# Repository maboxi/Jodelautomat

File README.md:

# Jodelautomat

Der Jodelautomat ist eine Musikbox, welche ohne professionelles Vorwissen entworfen und gebaut wurde.
Das Ziel dieses Repositories ist es, einzelne Aspekte des Jodelautomats neu zu entwerfen, um letztendlich eine verbesserte Version bauen zu können.

## Was kann der Jodelautomat alles?

Derzeit hat der Jodelautomat zwei Funktionen:
 - Musik wiedergeben: der Jodelautomat besitzt einen 3.5mm Klinkeneingang, welcher einen Verstärker (2x50W Main Drivers+ 100W Subwoofer) nutzt, um über zwei in das Gehäuse eingebaute Lautsprecher und einen in den Gehäuseboden integrierten Subwoofer Musik abzuspielen
 - LED-Beleuchtung: der Jodelautomat besitzt 3 LED-Bereiche (unten am Gehäuse, an den zwei Hauptlautsprechern an der Vorderseite und an der Bedienfläche des Jodelautomats), deren Farben entweder manuell ausgewählt oder von einem Mikrocontroller (für "Sound-To-Light") angesteuert werden können; das alte Sound-To-Light-System funtioniert jedoch nur grenzwertig

## Was soll der Jodelautomat alles können?

Ideen für Funktionen (+ Status):
 - Musik-Wiedergabe über Bluetooth
 - (WIP) Funktionierendes Sound-To-Light + LED-Ansteuerung: **JAVS** = Jodelautomat Visual System
 - besseres Gehäuse (leichter, an gewählte Lautsprecher angepasst)
 - neuen Akku + Ladefunktion + Netzadapter

## Repo TODO:
 - Bilder

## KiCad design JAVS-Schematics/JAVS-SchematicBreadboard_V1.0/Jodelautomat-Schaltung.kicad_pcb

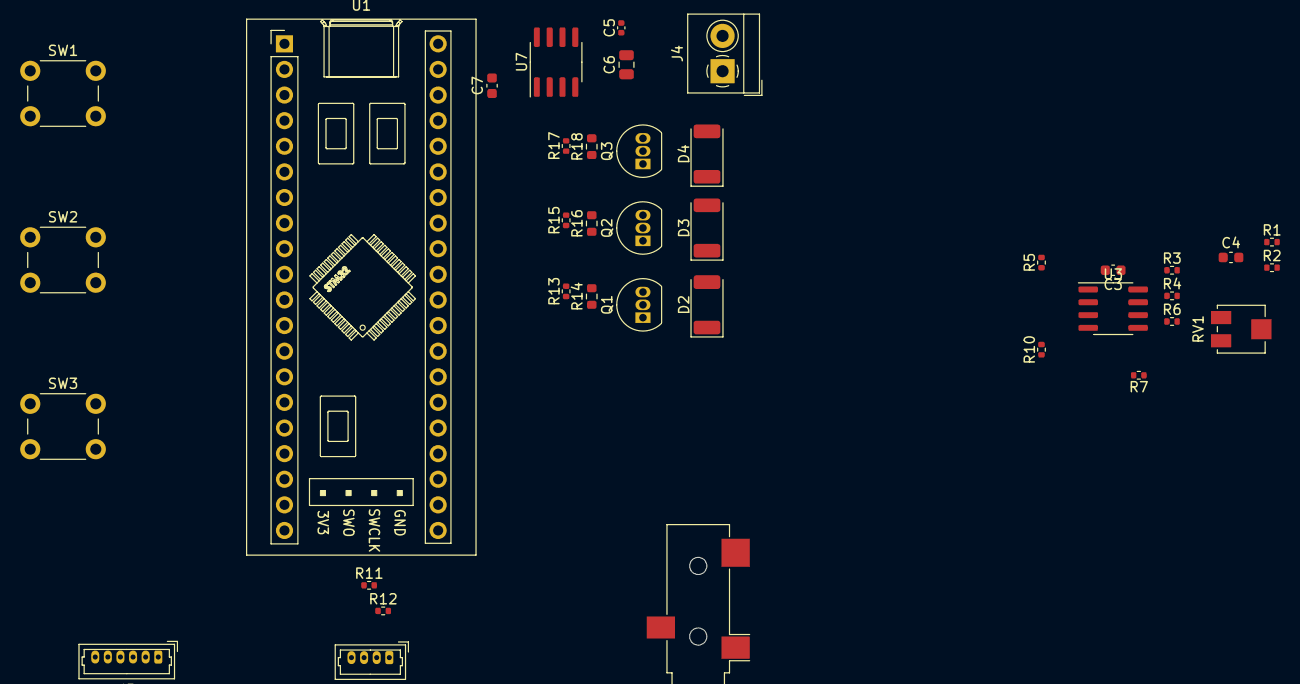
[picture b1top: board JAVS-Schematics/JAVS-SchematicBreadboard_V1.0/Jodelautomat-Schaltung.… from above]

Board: 2 copper layers, 38 parts (0 on the bottom side), 33 nets, no tracks yet.

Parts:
C3: 100n; C_0603_1608Metric
C4, C7: 10u; C_0603_1608Metric
C5: 10uF; C_0402_1005Metric
C6: 10uF; C_0805_2012Metric
D2: LED_R; LED_2010_5025Metric
D3: LED_G; LED_2010_5025Metric
D4: LED_B; LED_2010_5025Metric
J1: AudioJack3; Jack_3.5mm_CUI_SJ-3523-SMT_Horizontal
J2: I2C_5V_01x04; Molex_PicoBlade_53047-0410_1x04_P1.25mm_Vertical
J4: Screw_Terminal_01x02; TerminalBlock_4Ucon_1x02_P3.50mm_Horizontal
J5: USART_Full_01x06; Molex_PicoBlade_53047-0610_1x06_P1.25mm_Vertical
Q1, Q2, Q3: BC337; TO-92_Inline
R1, R2: 50k; R_0402_1005Metric
R3, R4, R5, R6, R7, R10: 100k; R_0402_1005Metric
R11, R12, R13, R15, R17: 10k; R_0402_1005Metric
R14: 120R; R_0603_1608Metric
R16, R18: 30R; R_0603_1608Metric
RV1: 100k; Potentiometer_Bourns_3314J_Vertical
SW1: BTN_A; SW_PUSH_6mm
SW2: BTN_B; SW_PUSH_6mm
SW3: BTN_C; SW_PUSH_6mm
U1: BlackPill_F401CCU6_SORTED; BlackPill_F401CCU6
U3: LM358; SOIC-8_3.9x4.9mm_P1.27mm
U7: ICL7660; SOIC-8_3.9x4.9mm_P1.27mm

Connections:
+3.3V: C7.1, D2.2 (A), D3.2 (A), D4.2 (A), J5.4, R10.1, U1.20 (3.3V), U1.21 (VBAT), U1.38 (3.3V)
+5V: C3.2, C4.2, J2.3, J4.1, R11.1, R12.1, U1.18 (5V), U1.40 (5V), U3.4 (V-), U7.8 (V+)
-5V: C3.1, C4.1, C6.2, U3.8 (V+), U7.5 (VOUT)
ADC_IN: R6.2, U1.28 (A2), U3.1
BTN_A: SW1.1, U1.1 (B12)
BTN_B: SW2.1, U1.2 (B13)
BTN_C: SW3.1, U1.3 (B14)
GND: C6.1, C7.2, J1.T, J2.4, J4.2, J5.6, R5.2, R14.1, R16.1, R18.1, SW1.2, SW2.2, SW3.2, U1.19 (G), U1.39 (G), U3.3 (+), U3.5 (+), U7.3 (GND)
LED_1_B: R17.1, U1.35 (B1)
LED_1_G: R15.1, U1.34 (B0)
LED_1_R: R13.1, U1.29 (A3)
unnamed: D2.1 (K), Q1.1 (C)
unnamed: D3.1 (K), Q2.1 (C)
unnamed: D4.1 (K), Q3.1 (C)
unnamed: J1.R, R2.1
unnamed: J1.S, R1.1
unnamed: J2.1, R12.2
unnamed: J2.2, R11.2
unnamed: Q1.2 (B), R13.2
unnamed: Q1.3 (E), R14.2
unnamed: Q2.2 (B), R15.2
unnamed: Q2.3 (E), R16.2
unnamed: Q3.2 (B), R17.2
unnamed: Q3.3 (E), R18.2
unnamed: R1.2, R2.2, RV1.1
unnamed: R3.1, R4.2, U3.7
unnamed: R5.1, R7.1, R10.2
unnamed: R3.2, R6.1, U3.2 (-)
unnamed: R4.1, R7.2, RV1.3, U3.6 (-)
unnamed: C5.1, U7.2 (CAP+)
unnamed: C5.2, U7.4 (CAP-)
USART_RX: J5.3, U1.7 (A10)
USART_TX: J5.2, U1.6 (A9)

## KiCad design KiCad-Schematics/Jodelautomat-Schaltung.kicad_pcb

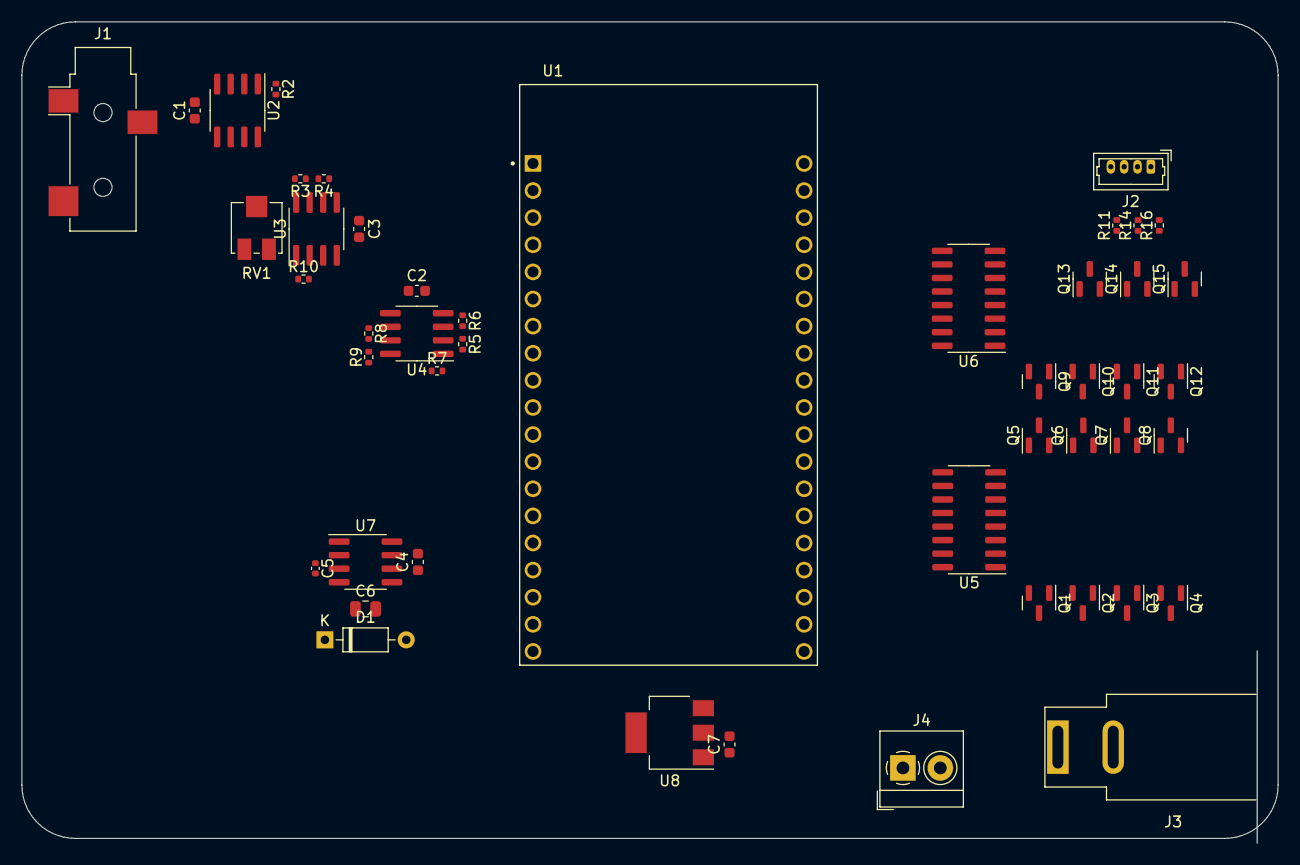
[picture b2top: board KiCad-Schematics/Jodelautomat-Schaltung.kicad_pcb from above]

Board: 2 copper layers, 117.7 x 76.9 mm, 49 parts (1 on the bottom side), 46 nets, no tracks yet.

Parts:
C1, C2, C3: 100n; C_0603_1608Metric
C4, C7: 10u; C_0603_1608Metric
C5: 10uF; C_0402_1005Metric
C6: 10uF; C_0805_2012Metric
D1: 1N914; D_DO-35_SOD27_P7.62mm_Horizontal
J1: AudioJack3; Jack_3.5mm_CUI_SJ-3523-SMT_Horizontal
J2: Conn_01x04_Pin; Molex_PicoBlade_53047-0410_1x04_P1.25mm_Vertical
J3: Barrel_Jack; BarrelJack_SwitchcraftConxall_RAPC10U_Horizontal
J4: Screw_Terminal_01x02; TerminalBlock_4Ucon_1x02_P3.50mm_Horizontal
Q1, Q2, Q3, Q4, Q5, Q6, Q7, Q8, Q9, Q10, Q11, Q12: MMBT3904; SOT-23
Q13, Q14, Q15: AO3400A; SOT-23
R1, R2, R4, R5, R6, R7, R8, R9, R10, R11, R14, R16: 100k; R_0402_1005Metric
R3: 10k; R_0402_1005Metric
RV1: 100k; Potentiometer_Bourns_3314J_Vertical
U1: ESP32-DEVKITC-32D; MODULE_ESP32-DEVKITC-32D
U2, U3, U4: LM358; SOIC-8_3.9x4.9mm_P1.27mm
U5, U6: 74HC595; SOIC-16_3.9x9.9mm_P1.27mm
U7: ICL7660; SOIC-8_3.9x4.9mm_P1.27mm
U8: AMS1117-5.0; SOT-223-3_TabPin2

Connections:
+3.3V: Q1.3 (C), Q5.3 (C), Q9.3 (C), R5.2, U1.J2-1 (3V3), U5.16 (VCC), U6.16 (VCC)
+5V: C7.2, U1.J2-19 (EXT_5V), U8.2 (VO)
+12V: C1.2, C2.2, C3.2, C4.2, J2.4, J3.1, J4.1, U2.4 (V-), U3.4 (V-), U4.4 (V-), U7.8 (V+), U8.3 (VI)
-12V: C1.1, C2.1, C3.1, C4.1, C6.2, D1.2 (A), U2.8 (V+), U3.8 (V+), U4.8 (V+), U7.5 (VOUT)
ADC_IN: R10.1, U1.J2-5 (IO34), U3.1
GND: C6.1, C7.1, D1.1 (K), J1.T, J3.2, J4.2, Q13.2 (S), Q14.2 (S), Q15.2 (S), R6.1, R11.2, R14.2, R16.2, RV1.2, U1.J2-14 (GND1), U1.J3-1 (GND3), U1.J3-7 (GND2), U3.3 (+), U3.5 (+), U4.5 (+), U5.8 (GND), U5.13 (~OE), U6.8 (GND), U6.13 (~OE), U7.3 (GND), U8.1 (GND)
LEDS_1_B: Q1.2 (E), Q2.2 (E), Q3.2 (E), Q4.2 (E), Q15.1 (G), R11.1
LEDS_1_G: Q5.2 (E), Q6.2 (E), Q7.2 (E), Q8.2 (E), Q14.1 (G), R14.1
LEDS_1_R: Q9.2 (E), Q10.2 (E), Q11.2 (E), Q12.2 (E), Q13.1 (G), R16.1
unnamed: J2.1, Q15.3 (D)
unnamed: J2.2, Q14.3 (D)
unnamed: J2.3, Q13.3 (D)
unnamed: Q1.1 (B), U5.15 (QA)
unnamed: Q2.1 (B), U5.1 (QB)
unnamed: Q3.1 (B), U5.2 (QC)
unnamed: Q4.1 (B), U5.3 (QD)
unnamed: Q5.1 (B), U5.7 (QH)
unnamed: Q6.1 (B), U5.6 (QG)
unnamed: Q7.1 (B), U5.5 (QF)
unnamed: Q8.1 (B), U5.4 (QE)
unnamed: Q9.1 (B), U6.15 (QA)
unnamed: Q10.1 (B), U6.1 (QB)
unnamed: Q11.1 (B), U6.2 (QC)
unnamed: Q12.1 (B), U6.3 (QD)
unnamed: R3.1, R4.2, U3.7
unnamed: R3.2, RV1.1
unnamed: R8.2, R9.2, U4.7
unnamed: J1.S, U2.3 (+)
unnamed: R2.1, U2.1, U2.2 (-)
unnamed: J1.R, U2.5 (+)
unnamed: R1.1, U2.6 (-), U2.7
unnamed: R9.1, R10.2, RV1.3, U3.2 (-)
unnamed: R1.2, R2.2, R4.1, U3.6 (-)
unnamed: R5.1, R6.2, U4.3 (+)
unnamed: R7.2, U4.1, U4.2 (-)
unnamed: R7.1, R8.1, U4.6 (-)
unnamed: U5.9 (QH'), U6.14 (SER)
unnamed: C5.1, U7.2 (CAP+)
unnamed: C5.2, U7.4 (CAP-)
PWM_OUT_1: Q2.3 (C), Q6.3 (C), Q10.3 (C), U1.J3-15 (IO2)
PWM_OUT_2: Q3.3 (C), Q7.3 (C), Q11.3 (C), U1.J3-14 (IO0)
PWM_OUT_3: Q4.3 (C), Q8.3 (C), Q12.3 (C), U1.J3-13 (IO4)
SHREG_CLK: U1.J3-10 (IO5), U5.11 (SRCLK), U6.11 (SRCLK)
SHREG_CLR: U1.J3-8 (IO19), U5.10 (~SRCLR), U6.10 (~SRCLR)
SHREG_INPUT: U1.J3-11 (IO17), U5.14 (SER)
STREG_CLK: U1.J3-9 (IO18), U5.12 (RCLK), U6.12 (RCLK)

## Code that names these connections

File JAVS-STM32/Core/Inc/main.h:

/* USER CODE BEGIN Header */
/**
  ******************************************************************************
  * @file           : main.h
  * @brief          : Header for main.c file.
  *                   This file contains the common defines of the application.
  ******************************************************************************
  * @attention
  *
  * Copyright (c) 2023 STMicroelectronics.
  * All rights reserved.
  *
  * This software is licensed under terms that can be found in the LICENSE file
  * in the root directory of this software component.
  * If no LICENSE file comes with this software, it is provided AS-IS.
  *
  ******************************************************************************
  */
/* USER CODE END Header */

/* Define to prevent recursive inclusion -------------------------------------*/
#ifndef __MAIN_H
#define __MAIN_H

#ifdef __cplusplus
extern "C" {
#endif

/* Includes ------------------------------------------------------------------*/
#include "stm32f4xx_hal.h"

/* Private includes ----------------------------------------------------------*/
/* USER CODE BEGIN Includes */

#include "LCD_PCF8574.h"
#include "LEDConfigMenu.h"

/* USER CODE END Includes */

/* Exported types ------------------------------------------------------------*/
/* USER CODE BEGIN ET */

/* USER CODE END ET */

/* Exported constants --------------------------------------------------------*/
/* USER CODE BEGIN EC */

/* USER CODE END EC */

/* Exported macro ------------------------------------------------------------*/
/* USER CODE BEGIN EM */

/* USER CODE END EM */

/* Exported functions prototypes ---------------------------------------------*/
void Error_Handler(void);

/* USER CODE BEGIN EFP */

void USB_PrintDebug(const char *str);
void IRQ_TIM11();
void Buttons_ResetFlags();

/* USER CODE END EFP */

/* Private defines -----------------------------------------------------------*/
#define LED_ONBOARD_Pin GPIO_PIN_13
#define LED_ONBOARD_GPIO_Port GPIOC
#define BTN_ONBOARD_Pin GPIO_PIN_0
#define BTN_ONBOARD_GPIO_Port GPIOA
#define LED_1_B_Pin GPIO_PIN_0
#define LED_1_B_GPIO_Port GPIOB
#define LED_1_G_Pin GPIO_PIN_1
#define LED_1_G_GPIO_Port GPIOB
#define LED_1_R_Pin GPIO_PIN_10
#define LED_1_R_GPIO_Port GPIOB
#define BTN_C_Pin GPIO_PIN_12
#define BTN_C_GPIO_Port GPIOB
#define BTN_B_Pin GPIO_PIN_13
#define BTN_B_GPIO_Port GPIOB
#define BTN_A_Pin GPIO_PIN_14
#define BTN_A_GPIO_Port GPIOB
#define LED_2_R_Pin GPIO_PIN_15
#define LED_2_R_GPIO_Port GPIOA
#define LED_2_G_Pin GPIO_PIN_3
#define LED_2_G_GPIO_Port GPIOB
#define LED_2_B_Pin GPIO_PIN_4
#define LED_2_B_GPIO_Port GPIOB
#define LED_3_R_Pin GPIO_PIN_5
#define LED_3_R_GPIO_Port GPIOB
#define LED_3_G_Pin GPIO_PIN_6
#define LED_3_G_GPIO_Port GPIOB
#define LED_3_B_Pin GPIO_PIN_7
#define LED_3_B_GPIO_Port GPIOB
/* USER CODE BEGIN Private defines */

/*
 *
 */

#define LCD_TIMEOUT 20000


/*
 * FFT Defines
 */
#define FFT_NUM_SAMPLES 4096
#define FFT_UARTBUFFERSIZE 512
#define FFT_UARTBUFFERFLAGBYTES 8

#define FFT_NODATA 		(1<<0)
#define FFT_CALLBACK_HALF 	(1<<1)
#define FFT_CALLBACK_FULL 	(1<<2)

/*
 * Button Defines
 */

#define BTN_EVENT_FLAG 1

#define BTN_A_FLAG 0
#define BTN_B_FLAG 1
#define BTN_C_FLAG 2

/*
 * Variables
 */


extern volatile uint32_t LCD_TimeoutCounter;

extern volatile uint8_t CDCReceiveFlag;
extern volatile uint32_t CDCReceiveDiscarded;
/* USER CODE END Private defines */

#ifdef __cplusplus
}
#endif

#endif /* __MAIN_H */

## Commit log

2023-04-20 adding existing project to repository
2023-04-20 moved invalid output data to new folder; invalid bc signal connected to wrong pin
2023-04-20 copied schematic files into git repo
2023-04-20 added uart fft output
2023-04-21 moving pins around to have a better breadboard layout
2023-04-21 copied KiCAD project for breadboard layout; removed big 3d files
2023-04-22 some modifications for breadboard creation; removed onboard leds for all stips except strip 1
2023-04-24 breadboard version was created and tested; resistor values for 3.3V/2 rail changed to 4.7k; added LTSpice simulations
2023-04-25 some more testing; changed fft cycles to 144 for testing
2023-04-26 changed pwm frequency from 100Hz to 1kHz
2023-04-26 cleaned project
2023-04-27 added first testing python script for fft data transmission
2023-04-28 created simple matplotlib visualizer that reads mc uart output; found problem with fft (only ~1 out of 3 ffts is correct, rest has alot of noise)
2023-04-30 reworked adc reading conversion and fft calculation; live visualizer using matplotlib now working and plotting fft power + phase
2023-05-01 plotting fft data with recursive running max
2023-05-02 renamed schematics folder since it not only contains KiCAD files but also breadboard layout information
2023-05-02 removed unused & invalid output data
2023-05-02 removed breadboard KiCAD project since my attempt to use it for breadboard creation wasn't too useful
2023-05-02 moved fft stuff to seperate header/source files
2023-05-02 restructured main file; no functional changes
2023-05-03 added first version of readme
